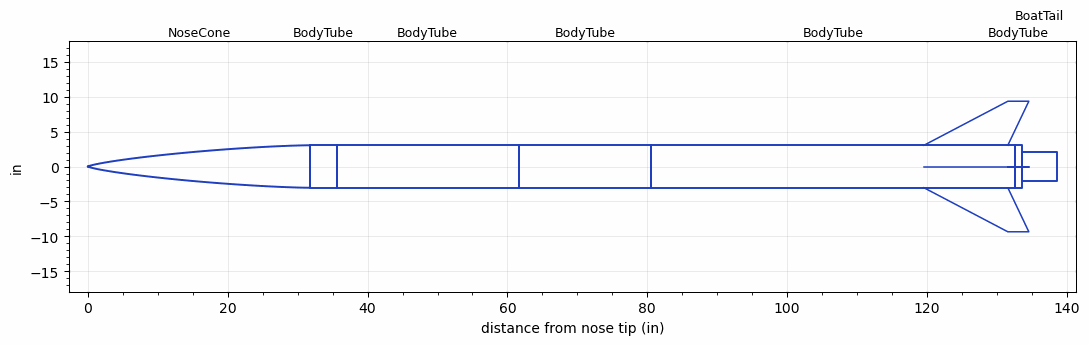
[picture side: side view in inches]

<RASAeroDocument>
 <FileVersion>2</FileVersion>
 <RocketDesign>
  <NoseCone>
   <Length>31.7499</Length>
   <Diameter>6.08</Diameter>
   <Shape>Von Karman Ogive</Shape>
   <Location>0</Location>
  </NoseCone>
  <BodyTube>
   <Length>3.85</Length>
   <Diameter>6.08</Diameter>
   <Location>31.7499</Location>
  </BodyTube>
  <BodyTube>
   <Length>25.9999</Length>
   <Diameter>6.08</Diameter>
   <Location>35.5999</Location>
  </BodyTube>
  <BodyTube>
   <Length>19</Length>
   <Diameter>6.08</Diameter>
   <RailGuideDiameter>0.62</RailGuideDiameter>
   <RailGuideHeight>0.383</RailGuideHeight>
   <Location>61.5999</Location>
  </BodyTube>
  <BodyTube>
   <Length>51.9999</Length>
   <Diameter>6.08</Diameter>
   <RailGuideDiameter>0.62</RailGuideDiameter>
   <RailGuideHeight>0.383</RailGuideHeight>
   <Location>80.5998</Location>
   <Fin>
    <Count>4</Count>
    <Chord>12</Chord>
    <Span>6.3</Span>
    <SweepDistance>12</SweepDistance>
    <TipChord>3</TipChord>
    <Thickness>0.3</Thickness>
    <Location>13</Location>
    <AirfoilSection>Subsonic NACA</AirfoilSection>
   </Fin>
  </BodyTube>
  <BodyTube>
   <Length>1</Length>
   <Diameter>6.08</Diameter>
   <Location>132.5997</Location>
  </BodyTube>
  <BoatTail>
   <Length>5</Length>
   <Diameter>4.1</Diameter>
   <RearDiameter>4.1</RearDiameter>
   <Location>133.5997</Location>
  </BoatTail>
  <Surface>Rough Camouflage Paint</Surface>
  <CD>0</CD>
  <ModifiedBarrowman>False</ModifiedBarrowman>
  <Turbulence>False</Turbulence>
  <UseBooster1>False</UseBooster1>
  <UseBooster2>False</UseBooster2>
  <Comments>Static bulkhead adjusted to match symmetry of dynamic bulkhead
</Comments>
 </RocketDesign>
 <LaunchSite>
  <Altitude>890</Altitude>
  <Pressure>28.9819</Pressure>
  <RodAngle>6</RodAngle>
  <RodLength>10.8333</RodLength>
  <Temperature>55.8261</Temperature>
  <WindSpeed>0</WindSpeed>
 </LaunchSite>
 <Recovery>
  <Altitude1>1500</Altitude1>
  <Altitude2>656.168</Altitude2>
  <DeviceType1>Parachute</DeviceType1>
  <DeviceType2>Parachute</DeviceType2>
  <Event1>True</Event1>
  <Event2>True</Event2>
  <Size1>83.9998</Size1>
  <Size2>23</Size2>
  <EventType1>Altitude</EventType1>
  <EventType2>Apogee</EventType2>
  <CD1>1.55</CD1>
  <CD2>0</CD2>
 </Recovery>
 <SimulationList>
  <Simulation>
   <SustainerLaunchWt>63.9635</SustainerLaunchWt>
   <SustainerCG>93.2873</SustainerCG>
   <SustainerIgnitionDelay>0</SustainerIgnitionDelay>
   <Booster1SeparationDelay>0</Booster1SeparationDelay>
   <Booster1IgnitionDelay>0</Booster1IgnitionDelay>
   <IncludeBooster1>False</IncludeBooster1>
   <Booster2Delay>0</Booster2Delay>
   <IncludeBooster2>False</IncludeBooster2>
  </Simulation>
 </SimulationList>
</RASAeroDocument>
